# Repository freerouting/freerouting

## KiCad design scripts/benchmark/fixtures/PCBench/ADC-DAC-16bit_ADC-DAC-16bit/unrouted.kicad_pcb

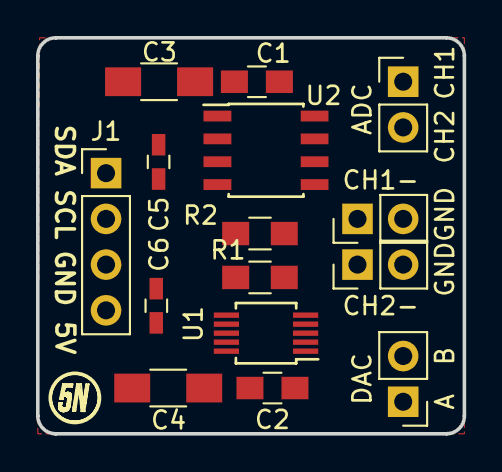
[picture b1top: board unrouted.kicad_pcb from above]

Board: 2 copper layers, 23.7 x 22.0 mm, 16 parts (1 on the bottom side), 11 nets, no tracks yet.

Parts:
C1, C2: 100n; C_0805_HandSoldering
C3, C4: 10u; C_1206_HandSoldering
C5, C6: 100n; C_0603_HandSoldering
J1: CON; Pin_Header_Straight_1x04_Pitch2.54mm
J2: DAC; Pin_Header_Straight_1x02_Pitch2.54mm
J3: ADC; Pin_Header_Straight_1x02_Pitch2.54mm
J4: CH1-; Pin_Header_Straight_1x02_Pitch2.54mm
J5: CH2-; Pin_Header_Straight_1x02_Pitch2.54mm
R1, R2: 4K7; R_0805_HandSoldering
TP1: DAC Vref; Measurement_Point_Round-SMD-Pad_Small
U1: AD5667R; MSOP-10_3x3mm_Pitch0.5mm
U2: MCP3426; SOIC-8_3.9x4.9mm_Pitch1.27mm

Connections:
+5V: C1.1, C2.1, C3.1, C4.1, C5.1, C6.1, J1.4, R1.1, R2.1, U1.5, U1.9, U2.3
GND: C1.2, C2.2, C3.2, C4.2, C5.2, C6.2, J1.3, J4.2, J5.2, U1.3, U1.4, U1.6, U2.6
unnamed: J1.1, R1.2, U1.8, U2.4
unnamed: J1.2, R2.2, U1.7, U2.5
unnamed: J2.1, U1.1
unnamed: J2.2, U1.2
unnamed: J3.1, U2.1
unnamed: J3.2, U2.7
unnamed: J4.1, U2.2
unnamed: J5.1, U2.8
unnamed: TP1.1, U1.10

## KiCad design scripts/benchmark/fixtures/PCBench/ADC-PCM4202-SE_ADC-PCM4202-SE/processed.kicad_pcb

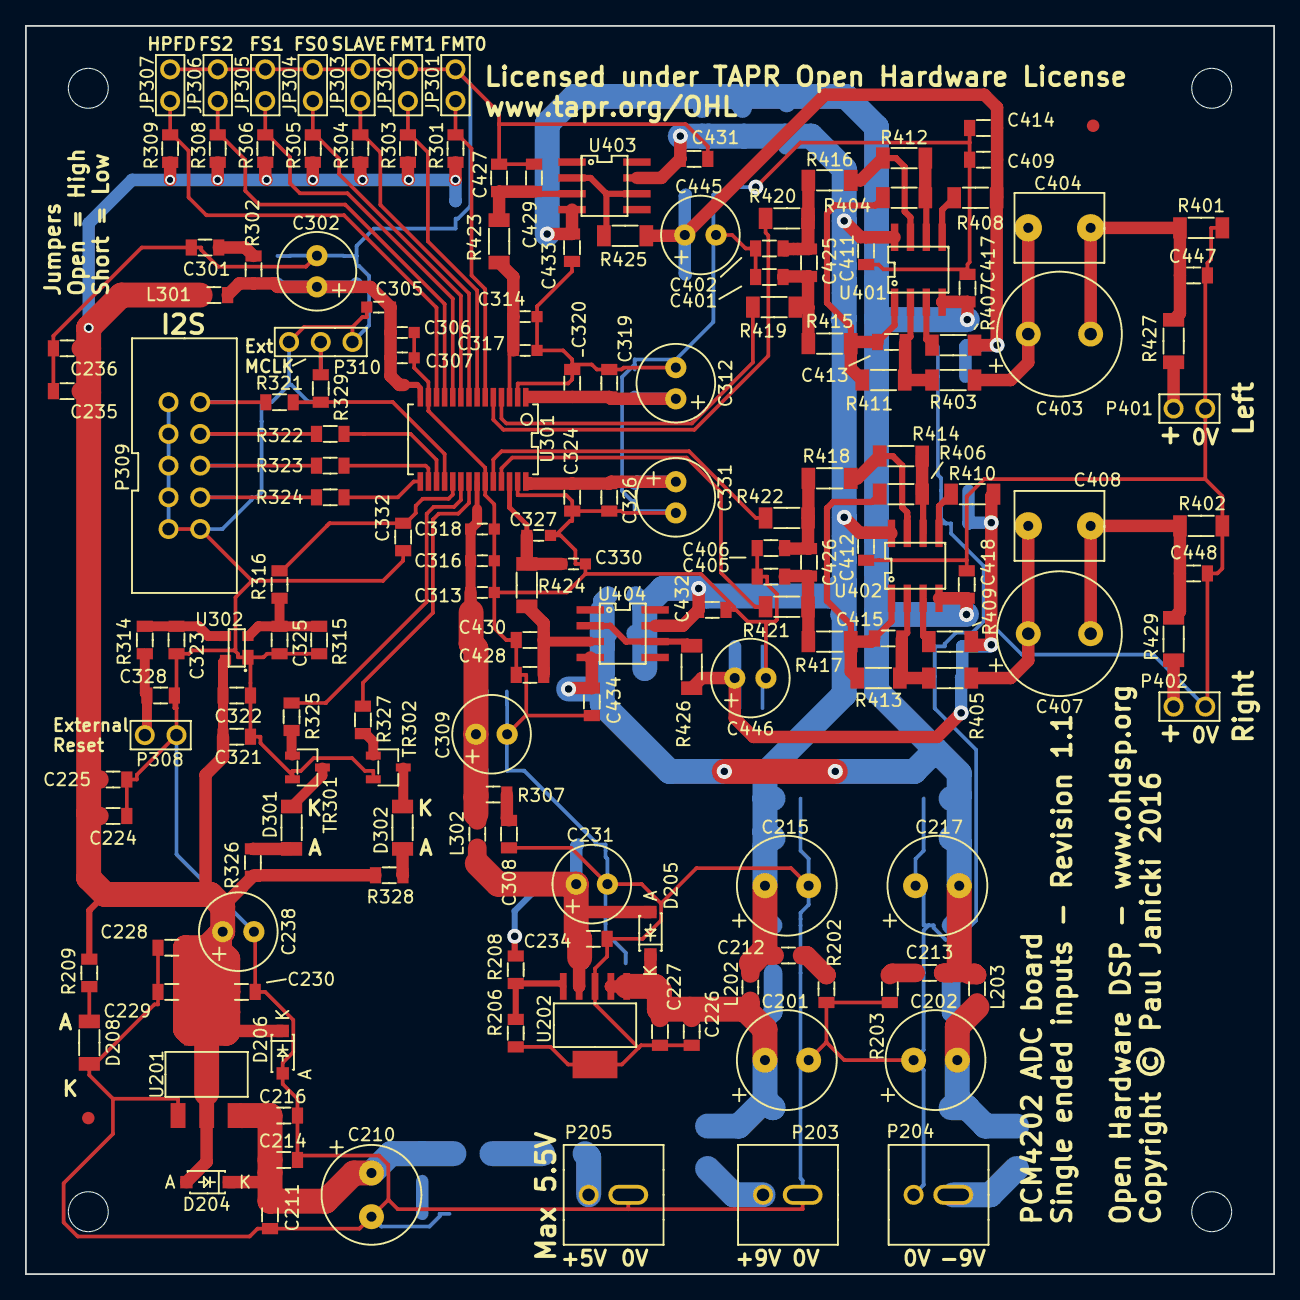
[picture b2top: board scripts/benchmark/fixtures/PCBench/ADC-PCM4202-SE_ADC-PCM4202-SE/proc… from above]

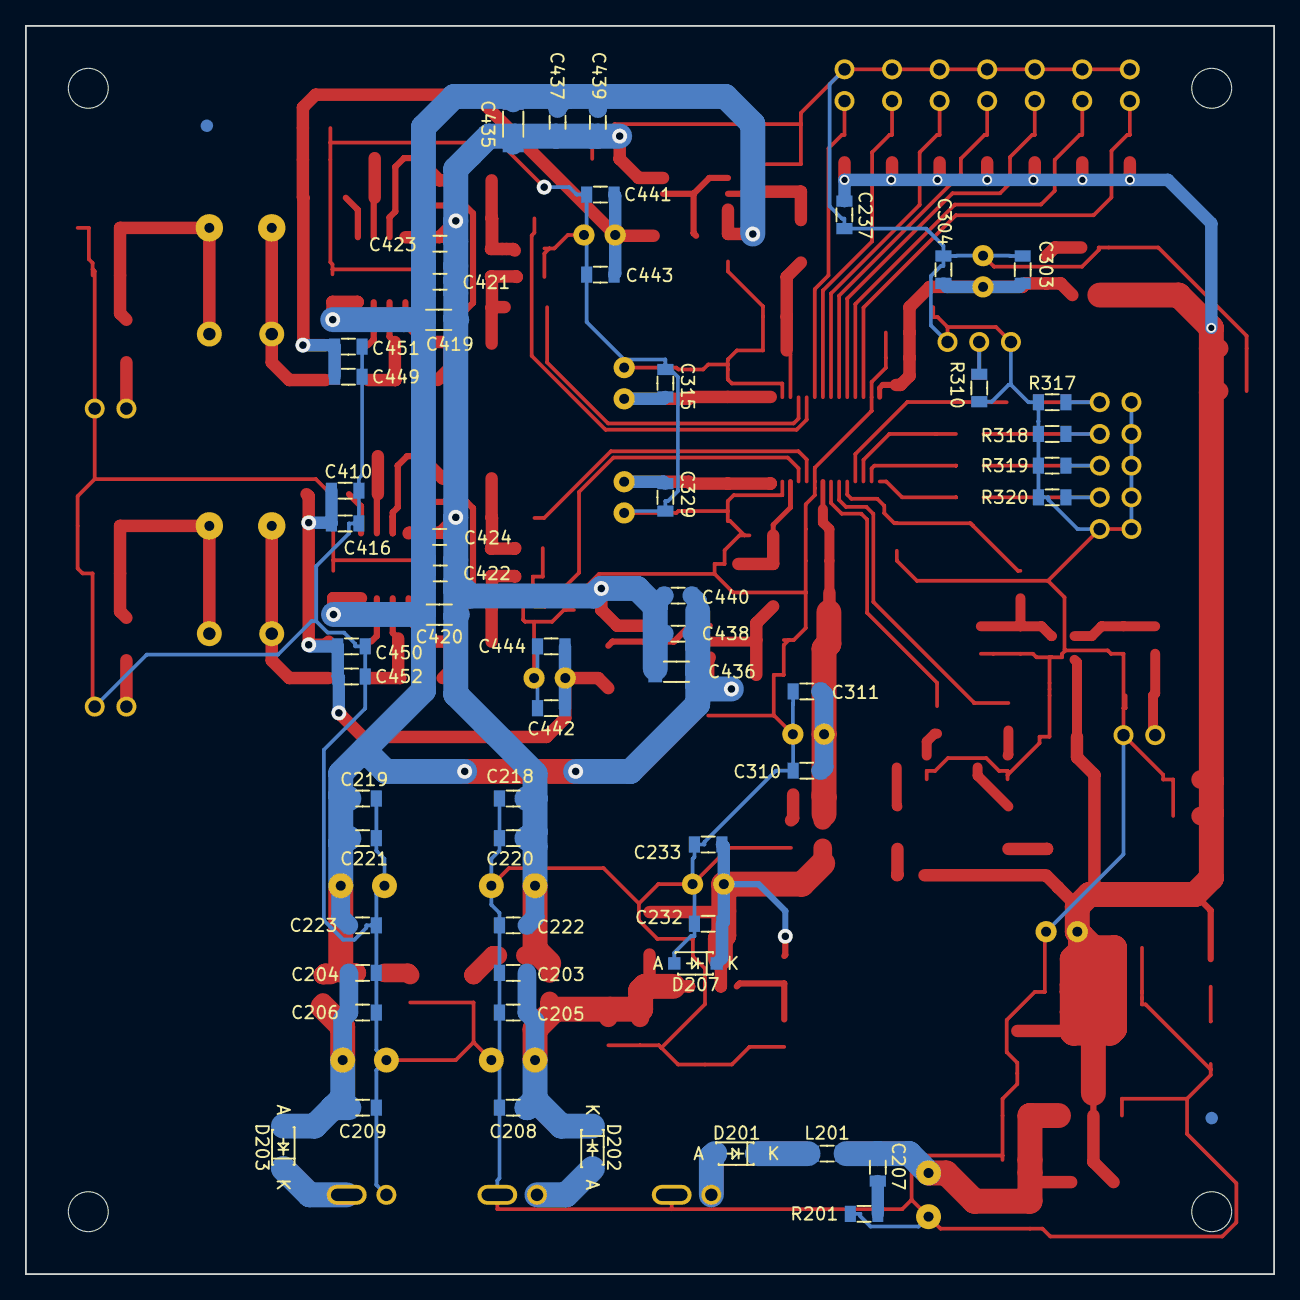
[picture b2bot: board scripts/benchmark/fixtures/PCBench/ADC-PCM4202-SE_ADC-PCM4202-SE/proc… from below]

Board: 2 copper layers, 100.0 x 100.0 mm, 230 parts (57 on the bottom side), 85 nets.

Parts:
C201, C202, C210, C215, C217: 220u; CAP-TH-D8mmP3.5mm
C203, C204, C211, C218, C219, C226, C228, C232, C303, C310, C315, C329: 22u; SMD-0805
C205, C206, C214, C220, C221, C225, C227, C229, C233, C236, C237, C304, C311, C319, C322, C323, C326, C328, C332, C409, C410, C411, C412, C417, C418, C421, C422, C427, C428, C431, C432, C433, C434, C437, C438, C441, C442, C449, C450: 100n; SMD-0805
C207, C212, C213, C301, C308, C401, C402, C405, C406: 100p; SMD-0805
C208, C209, C216, C222, C223, C230, C234, C320, C324, C423, C424, C429, C430, C439, C440, C443, C444: 10n; SMD-0805
C224, C235, C321, C414, C416, C451, C452: 10u; SMD-0805
C231, C238, C302, C309, C312, C331: 220u; CAP-TH-D6.3mmP2.5mm
C305, C313: 1u; SMD-0603
C306, C314, C316, C330: 100n; SMD-0603
C307, C317, C318, C327: 10n; SMD-0603
C325: N/F; SMD-0805
C403, C407: 100u; CAP-TH-D10mmP5mm
C404, C408: 100n; CAP_TH_5mm
C413, C415: 330p; SMD-0805
C419, C420, C435, C436: 10u; SMD-1206
C425, C426: 2n7; SMD-0805
C445, C446: 47u; CAP-TH-D6.3mmP2.5mm
C447, C448: 1n; SMD-0805
D201, D202, D203, D204, D205, D206, D207: SS14L; DIODE-SOD-123
D208: Green LED 1206; SMD-1206
D301, D302: Red LED 1206; SMD-1206
FID1, FID2, FID3, FID4: MNT_HOLE; FID-1MM-3MM
JP301, JP302, JP303, JP304, JP305, JP306, JP307: CONN_2x1; CONN_SIL_2_1MM
L201, L202, L203, L301, L302: 600R@100MHz; SMD-0805
MNT201, MNT202, MNT203, MNT204: MNT_HOLE; MNT_HOLE_3.2mm
P203, P204, P205: CONN_2x1; CONN-2WAY-2.54mm-3.81mm-SPACING
P308, P401, P402: CONN_2x1; CONN_SIL_2_1MM
P309: CONN_02X05; CONN_DIL_2X5_BOX_1MM
P310: N/F; CONN_SIL_3_1MM
R201, R202, R203, R302, R307: 47; SMD-0805
R206: 2k2; SMD-0805
R208: 6k8; SMD-0805
R209, R326, R328: 470; SMD-0805
R301, R303, R304, R305, R306, R308, R309: 10k; SMD-0805
R310, R317, R318, R319, R320, R329: N/F; SMD-0805
R314, R325, R327: 1k; SMD-0805
R315: 100k; SMD-0805
R316: 100R; SMD-0805
R321, R322, R323: 0; SMD-0805
R324: 75; SMD-0805
R401, R402: 47k; SMD-1206
R403, R405, R423, R424, R425, R426, R427, R429: 1k; SMD-1206
R404, R406, R412, R414: 1k5; SMD-1206
R407, R408, R409, R410, R411, R413: 2k2; SMD-1206
R415, R416, R417, R418: 40R2; SMD-1206
R419, R420: 100; SMD-1206
R421, R422: 100R; SMD-1206
TR301, TR302: BC847; IC-SOT23
U201: TLV1117LV33DCY; IC-SOT-223
U202: TPS7A4501; IC-SOT223-6
U301: PCM4202DBT; IC-SSOP28
U302: ADM811TART; IC-SOT143
U401, U402: TLE2072; IC_SOIC_8
U403, U404: TLE2071; IC_SOIC_8

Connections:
+9VA: C212.1, C215.1, C218.1, C220.1, C222.1, C411.1, C412.1, C419.1, C420.1, C421.1, C422.1, C423.1, C424.1, C431.1, C432.1, C435.1, C436.1, C437.1, C438.1, C439.1, C440.1, L202.2, U401.8, U402.8, U403.7, U404.7
-9VA: C213.2, C217.2, C219.2, C221.2, C223.2, C417.2, C418.2, C419.2, C420.2, C421.2, C422.2, C423.2, C424.2, C433.2, C434.2, C435.2, C436.2, C437.2, C438.2, C439.2, C440.2, L203.2, U401.4, U402.4, U403.4, U404.4
/InputFilters/ANAL+: R419.1, U301.4
/InputFilters/ANAL-: R420.1, U301.5
/InputFilters/ANAR+: R421.1, U301.25
/InputFilters/ANAR-: R422.1, U301.24
/InputFilters/VCML: C409.1, C414.1, C441.1, C443.1, C445.1, C449.1, C451.1, R407.2, R408.2, R425.1
/InputFilters/VCMR: C410.1, C416.1, C442.1, C444.1, C446.1, C450.1, C452.1, R409.2, R410.2, R426.1
/InputFilters/VCOML: C314.1, C317.1, R423.2, U301.3
/InputFilters/VCOMR: C327.1, C330.1, R424.2, U301.26
/PCM4202/ADC_RESET: C332.1, R316.1, U301.19
/PCM4202/AVCC: C309.1, C310.1, C311.1, C313.1, C316.1, C318.1, L302.2, R307.1, U301.22
/PCM4202/CLIPL: R327.1, U301.21
/PCM4202/CLIPR: R325.1, U301.20
/PCM4202/DVDD: C302.1, C303.1, C304.1, C305.1, C306.1, C307.1, L301.2, R302.1, U301.14
/PCM4202/FMT0: JP301.1, R301.2, U301.6
/PCM4202/FMT1: JP302.1, R303.2, U301.7
/PCM4202/FS0: JP304.1, R305.2, U301.9
/PCM4202/FS1: JP305.1, R306.2, U301.10
/PCM4202/FS2: JP306.1, R308.2, U301.11
/PCM4202/HPFD: JP307.1, R309.2, U301.12
/PCM4202/SLAVE: JP303.1, R304.2, U301.8
GNDA: C201.2, C202.1, C203.2, C204.1, C205.2, C206.1, C208.2, C209.1, C210.2, C211.2, C214.2, C215.2, C216.2, C217.1, C218.2, C219.1, C220.2, C221.1, C222.2, C223.1, C224.2, C225.2, C226.2, C227.2, C228.2, C229.2, C230.2, C231.2, C232.2, C233.2, C234.2, C235.2, C236.2, C237.2, C238.2, C301.2, C302.2, C303.2, C304.2, C305.2, C306.2, C307.2, C308.2, C309.2, C310.2, C311.2, C312.2, C313.2, C314.2, C315.2, C316.2, C317.2, C318.2, C319.2, C320.2, C321.2, C322.2, C323.2, C324.2, C325.2, C326.2, C327.2, C328.2, C329.2, C330.2, C331.2, C332.2, C401.1, C402.2, C405.1, C406.2, C409.2, C410.2, C411.2, C412.2, C414.2, C416.2, C417.1, C418.1, C427.2, C428.2, C429.2, C430.2, C431.2, C432.2, C433.1, C434.1, C441.2, C442.2, C443.2, C444.2, C445.2, C446.2, C447.2, C448.2, C449.2, C450.2, C451.2, C452.2, D206.1, D207.1, D208.2, JP301.2, JP302.2, JP303.2, JP304.2, JP305.2, JP306.2, JP307.2, P203.2, P204.1, P205.2, P308.2, P309.1, P309.3, P309.5, P309.7, P309.9, P309.10, P310.1, P310.3, P401.2, P402.2, R201.2, R202.2, R203.1, R206.2, R310.1, R315.1, R317.1, R318.1, R319.1, R320.1, R401.1, R402.1, TR301.2, TR302.2, U201.1, U202.3, U301.2, U301.13, U301.23, U301.27, U302.1
unnamed: C202.2, C204.2, C206.2, C209.2, D203.1, L203.1
unnamed: C207.1, C210.1, C211.1, C214.1, C216.1, D204.2, L201.2, U201.3
unnamed: C207.2, R201.1
unnamed: C212.2, R202.1
unnamed: C213.1, R203.2
unnamed: C301.1, R302.2
unnamed: C308.1, R307.2
unnamed: C312.1, C315.1, C319.1, C320.1, U301.1
unnamed: C323.1, R314.1, U302.3
unnamed: C324.1, C326.1, C329.1, C331.1, U301.28
unnamed: C325.1, R315.2, R316.2, U302.2
unnamed: C328.1, P308.1, R314.2
unnamed: C401.2, C425.1, R415.1, R419.2
unnamed: C402.1, C425.2, R416.1, R420.2
unnamed: C403.1, C404.2, R403.2
unnamed: C403.2, C404.1, C447.1, R401.2, R427.1
unnamed: C405.2, C426.1, R417.1, R421.2
unnamed: C406.1, C426.2, R418.1, R422.2
unnamed: C407.1, C408.2, R405.2
unnamed: C407.2, C408.1, C448.1, R402.2, R429.1
unnamed: C413.1, R403.1, R411.2, U401.2
unnamed: C413.2, R404.1, R411.1, R415.2, U401.1
unnamed: C415.1, R405.1, R413.2, U402.2
unnamed: C415.2, R406.1, R413.1, R417.2, U402.1
unnamed: C427.1, C429.1, R423.1, U403.3
unnamed: C428.1, C430.1, R424.1, U404.3
unnamed: D201.1, P205.1
unnamed: D201.2, L201.1
unnamed: D202.1, P203.1
unnamed: D203.2, P204.2
unnamed: D208.1, R209.1
unnamed: D301.1, R326.1
unnamed: D301.2, TR301.3
unnamed: D302.1, R328.1
unnamed: D302.2, TR302.3
unnamed: P309.2, R317.2, R321.1
unnamed: P309.4, R318.2, R322.1
unnamed: P309.6, R319.2, R323.1
unnamed: P309.8, R320.2, R324.1
unnamed: P310.2, R310.2, R329.1
unnamed: P401.1, R427.2
unnamed: P402.1, R429.2
unnamed: R206.1, R208.2, U202.5
unnamed: R321.2, R329.2, U301.18
unnamed: R322.2, U301.17
unnamed: R323.2, U301.16
unnamed: R324.2, U301.15
unnamed: R325.2, TR301.1
unnamed: R327.2, TR302.1
unnamed: R404.2, R412.2, U401.6
unnamed: R406.2, R414.2, U402.6
unnamed: R407.1, U401.3
unnamed: R408.1, U401.5
unnamed: R409.1, U402.3
unnamed: R410.1, U402.5
unnamed: R412.1, R416.2, U401.7
unnamed: R414.1, R418.2, U402.7
unnamed: R425.2, U403.2, U403.6
unnamed: R426.2, U404.2, U404.6
VAA: C231.1, C232.1, C233.1, C234.1, D205.1, D207.2, L302.1, R208.1, U202.4
VCC: C201.1, C203.1, C205.1, C208.1, C226.1, C227.1, D202.2, D205.2, L202.1, U202.1, U202.2
VDD: C224.1, C225.1, C228.1, C229.1, C230.1, C235.1, C236.1, C237.1, C238.1, C321.1, C322.1, D204.1, D206.2, L301.1, R209.2, R301.1, R303.1, R304.1, R305.1, R306.1, R308.1, R309.1, R326.2, R328.2, U201.2, U302.4

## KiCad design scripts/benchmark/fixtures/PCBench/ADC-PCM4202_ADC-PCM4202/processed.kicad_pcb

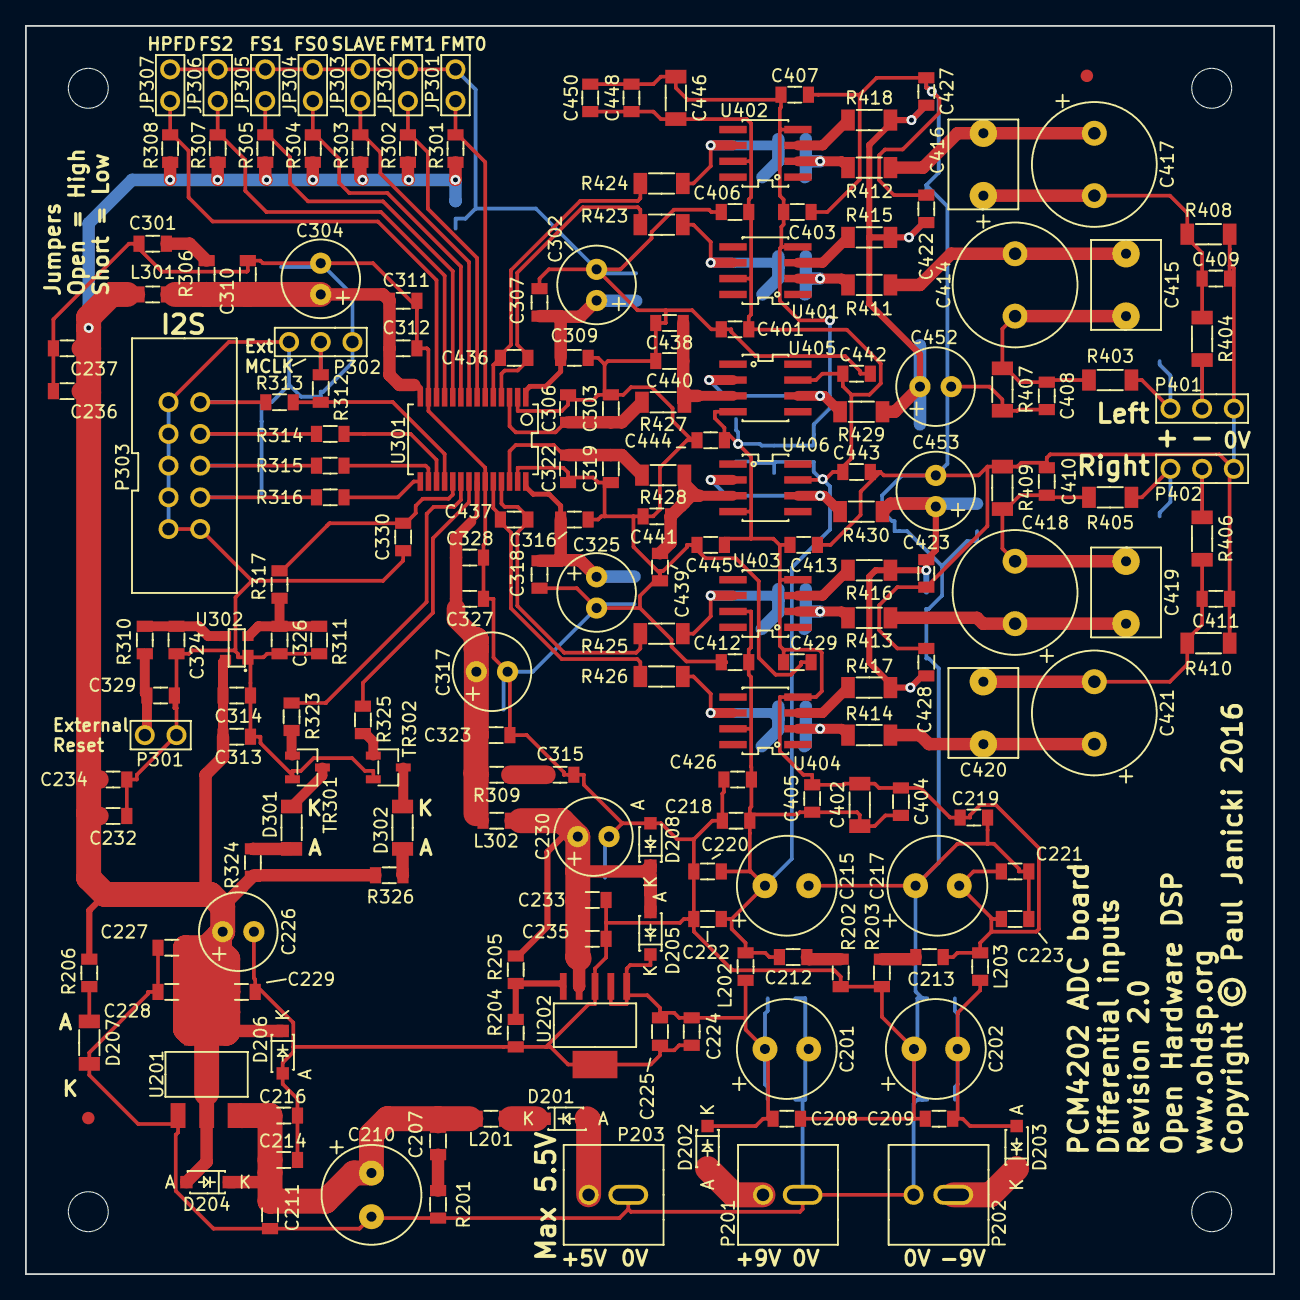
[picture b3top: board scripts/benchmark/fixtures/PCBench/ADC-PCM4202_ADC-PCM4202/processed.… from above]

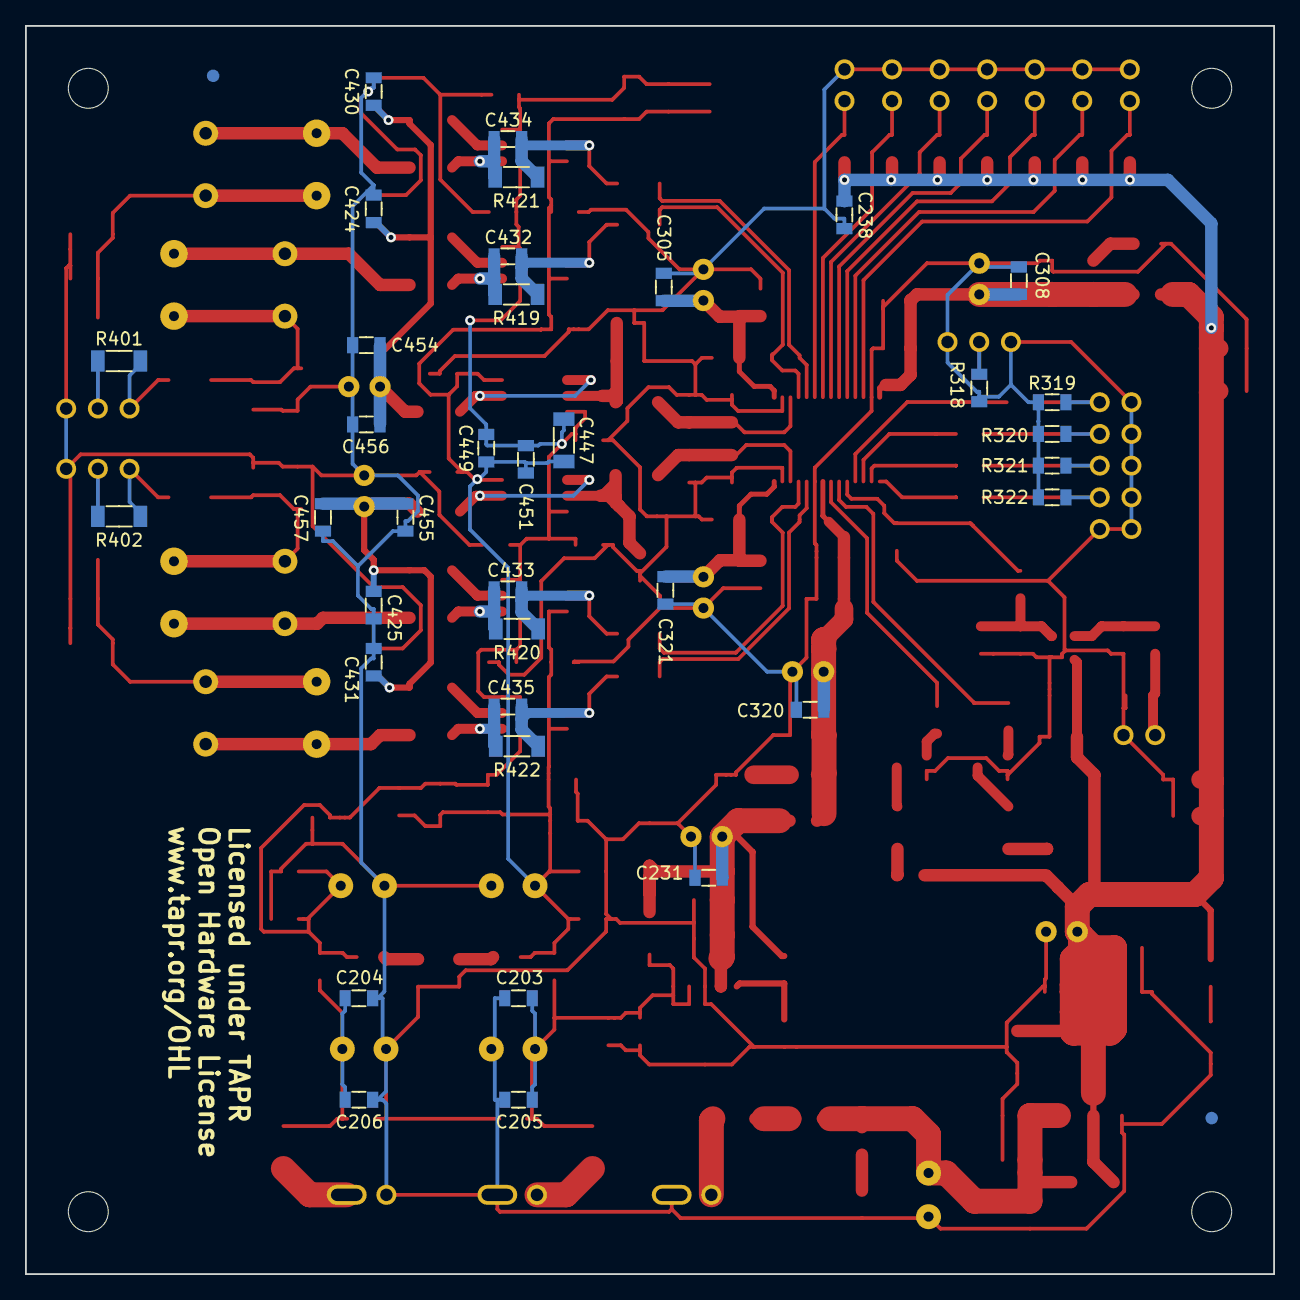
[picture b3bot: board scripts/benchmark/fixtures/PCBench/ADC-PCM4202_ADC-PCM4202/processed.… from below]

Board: 2 copper layers, 100.0 x 100.0 mm, 237 parts (38 on the bottom side), 87 nets.

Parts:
C201, C202, C210, C215, C217: 220u; CAP-TH-D8mmP3.5mm
C203, C204, C211, C218, C219, C224, C227, C231, C305, C308, C320, C321: 22u; SMD-0805
C205, C206, C214, C220, C221, C225, C228, C233, C234, C237, C238, C303, C307, C310, C311, C314, C318, C322, C323, C324, C327, C329, C330, C401, C403, C404, C406, C407, C412, C413, C422, C423, C426, C427, C428, C429, C438, C439, C442, C443, C444, C445, C448, C449, C454, C455: 100n; SMD-0805
C207, C212, C213, C301, C315, C408, C409, C410, C411: 100p; SMD-0805
C208, C209, C216, C222, C223, C229, C235, C306, C309, C312, C316, C319, C328, C405, C440, C441, C450, C451, C456, C457: 10n; SMD-0805
C226, C230, C302, C304, C317, C325: 220u; CAP-TH-D6.3mmP2.5mm
C232, C236, C313, C424, C425, C430, C431: 10u; SMD-0805
C326: N/F; SMD-0805
C402, C446, C447: 10u; SMD-1206
C414, C417, C418, C421: 100u; CAP-TH-D10mmP5mm
C415, C416, C419, C420: 100n; CAP_TH_5mm
C432, C433, C434, C435: 47p; SMD-0805
C436, C437: 2n7; SMD-0805
C452, C453: 47u; CAP-TH-D6.3mmP2.5mm
D201, D202, D203, D204, D205, D206, D208: SS14L; DIODE-SOD-123
D207: Green LED 1206; SMD-1206
D301, D302: Red LED 1206; SMD-1206
FID201, FID202, FID203, FID204: MNT_HOLE; FID-1MM-3MM
JP301, JP302, JP303, JP304, JP305, JP306, JP307: CONN_2x1; CONN_SIL_2_1MM
L201, L202, L203, L301, L302: 600R@100MHz; SMD-0805
MNT201, MNT202, MNT203, MNT204: MNT_HOLE; MNT_HOLE_3.2mm
P201, P202, P203: CONN_2x1; CONN-2WAY-2.54mm-3.81mm-SPACING
P301: CONN_2x1; CONN_SIL_2_1MM
P302: N/F; CONN_SIL_3_1MM
P303: CONN_02X05; CONN_DIL_2X5_BOX_1MM
P401, P402: CONN_3x1; CONN_SIL_3_1MM
R201, R202, R203, R306, R309: 47; SMD-0805
R204: 2k2; SMD-0805
R205: 6k8; SMD-0805
R206, R324, R326: 470; SMD-0805
R301, R302, R303, R304, R305, R307, R308: 10k; SMD-0805
R310, R323, R325: 1k; SMD-0805
R311: 100k; SMD-0805
R312, R318, R319, R320, R321, R322: N/F; SMD-0805
R313, R314, R315: 0; SMD-0805
R316: 75; SMD-0805
R317: 100R; SMD-0805
R401, R402, R419, R420, R421, R422: 10k; SMD-1206
R403, R404, R405, R406: 100; SMD-1206
R407, R408, R409, R410: 100k; SMD-1206
R411, R412, R413, R414, R415, R416, R417, R418: 4k7; SMD-1206
R423, R424, R425, R426: 40R2; SMD-1206
R427, R428, R429, R430: 1k; SMD-1206
TR301, TR302: BC847; IC-SOT23
U201: TLV1117LV33DCY; IC-SOT-223
U202: TPS7A4501; IC-SOT223-6
U301: PCM4202DBT; IC-SSOP28
U302: ADM811TART; IC-SOT143
U401, U402, U403, U404, U405, U406: TLE2071; IC_SOIC_8

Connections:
+9VA: C212.1, C215.1, C218.1, C220.1, C222.1, C401.1, C402.1, C404.1, C405.1, C406.1, C412.1, C426.1, C442.1, C443.1, C446.1, C447.1, C448.1, C449.1, C450.1, C451.1, L202.2, U401.7, U402.7, U403.7, U404.7, U405.7, U406.7
-9VA: C213.2, C217.2, C219.2, C221.2, C223.2, C402.2, C403.2, C404.2, C405.2, C407.2, C413.2, C429.2, C444.2, C445.2, C446.2, C447.2, C448.2, C449.2, C450.2, C451.2, L203.2, U401.4, U402.4, U403.4, U404.4, U405.4, U406.4
/InputFilters/ANAL+: C436.1, R423.1, U301.4
/InputFilters/ANAL-: C436.2, R424.1, U301.5
/InputFilters/ANAR+: C437.1, R425.1, U301.25
/InputFilters/ANAR-: C437.2, R426.1, U301.24
/InputFilters/VCML: C422.1, C424.1, C427.1, C430.1, C452.1, C454.1, C456.1, R415.1, R418.2, R429.1
/InputFilters/VCMR: C423.1, C425.1, C428.1, C431.1, C453.1, C455.1, C457.1, R416.1, R417.2, R430.1
/InputFilters/VCOML: C303.1, C306.1, R427.2, U301.3
/InputFilters/VCOMR: C319.1, C322.1, R428.2, U301.26
/PCM4202/ADC_RESET: C330.1, R317.1, U301.19
/PCM4202/AVCC: C317.1, C320.1, C323.1, C327.1, C328.1, L302.2, R309.1, U301.22
/PCM4202/CLIPL: R325.1, U301.21
/PCM4202/CLIPR: R323.1, U301.20
/PCM4202/DVDD: C304.1, C308.1, C310.1, C311.1, C312.1, L301.2, R306.1, U301.14
/PCM4202/FMT0: JP301.1, R301.2, U301.6
/PCM4202/FMT1: JP302.1, R302.2, U301.7
/PCM4202/FS0: JP304.1, R304.2, U301.9
/PCM4202/FS1: JP305.1, R305.2, U301.10
/PCM4202/FS2: JP306.1, R307.2, U301.11
/PCM4202/HPFD: JP307.1, R308.2, U301.12
/PCM4202/SLAVE: JP303.1, R303.2, U301.8
GNDA: C201.2, C202.1, C203.2, C204.1, C205.2, C206.1, C208.2, C209.1, C210.2, C211.2, C214.2, C215.2, C216.2, C217.1, C218.2, C219.1, C220.2, C221.1, C222.2, C223.1, C224.2, C225.2, C226.2, C227.2, C228.2, C229.2, C230.2, C231.2, C232.2, C233.2, C234.2, C235.2, C236.2, C237.2, C238.2, C301.2, C302.2, C303.2, C304.2, C305.2, C306.2, C307.2, C308.2, C309.2, C310.2, C311.2, C312.2, C313.2, C314.2, C315.2, C316.2, C317.2, C318.2, C319.2, C320.2, C321.2, C322.2, C323.2, C324.2, C325.2, C326.2, C327.2, C328.2, C329.2, C330.2, C401.2, C403.1, C406.2, C407.1, C408.2, C409.2, C410.2, C411.2, C412.2, C413.1, C422.2, C423.2, C424.2, C425.2, C426.2, C427.2, C428.2, C429.1, C430.2, C431.2, C438.2, C439.2, C440.2, C441.2, C442.2, C443.2, C444.1, C445.1, C452.2, C453.2, C454.2, C455.2, C456.2, C457.2, D206.1, D207.2, D208.1, JP301.2, JP302.2, JP303.2, JP304.2, JP305.2, JP306.2, JP307.2, P201.2, P202.1, P203.2, P301.2, P302.1, P302.3, P303.1, P303.3, P303.5, P303.7, P303.9, P303.10, P401.3, P402.3, R201.2, R202.2, R203.1, R204.2, R311.1, R318.1, R319.1, R320.1, R321.1, R322.1, R407.1, R408.1, R409.1, R410.1, TR301.2, TR302.2, U201.1, U202.3, U301.2, U301.13, U301.23, U301.27, U302.1
unnamed: C202.2, C204.2, C206.2, C209.2, D203.1, L203.1
unnamed: C207.1, C210.1, C211.1, C214.1, C216.1, D204.2, L201.2, U201.3
unnamed: C207.2, R201.1
unnamed: C212.2, R202.1
unnamed: C213.1, R203.2
unnamed: C301.1, R306.2
unnamed: C302.1, C305.1, C307.1, C309.1, U301.1
unnamed: C315.1, R309.2
unnamed: C316.1, C318.1, C321.1, C325.1, U301.28
unnamed: C324.1, R310.1, U302.3
unnamed: C326.1, R311.2, R317.2, U302.2
unnamed: C329.1, P301.1, R310.2
unnamed: C408.1, C414.2, C415.1, R403.1, R407.2
unnamed: C409.1, C416.1, C417.2, R404.1, R408.2
unnamed: C410.1, C418.2, C419.1, R405.1, R409.2
unnamed: C411.1, C420.1, C421.2, R406.1, R410.2
unnamed: C414.1, C415.2, R411.1
unnamed: C416.2, C417.1, R412.2
unnamed: C418.1, C419.2, R413.1
unnamed: C420.2, C421.1, R414.2
unnamed: C432.1, R411.2, R419.2, U401.2
unnamed: C432.2, R419.1, R423.2, U401.6
unnamed: C433.1, R413.2, R420.2, U403.2
unnamed: C433.2, R420.1, R425.2, U403.6
unnamed: C434.1, R412.1, R421.2, U402.2
unnamed: C434.2, R421.1, R424.2, U402.6
unnamed: C435.1, R414.1, R422.2, U404.2
unnamed: C435.2, R422.1, R426.2, U404.6
unnamed: C438.1, C440.1, R427.1, U405.3
unnamed: C439.1, C441.1, R428.1, U406.3
unnamed: D201.1, P203.1
unnamed: D201.2, L201.1
unnamed: D202.1, P201.1
unnamed: D203.2, P202.2
unnamed: D207.1, R206.1
unnamed: D301.1, R324.1
unnamed: D301.2, TR301.3
unnamed: D302.1, R326.1
unnamed: D302.2, TR302.3
unnamed: P302.2, R312.1, R318.2
unnamed: P303.2, R313.1, R319.2
unnamed: P303.4, R314.1, R320.2
unnamed: P303.6, R315.1, R321.2
unnamed: P303.8, R316.1, R322.2
unnamed: P401.1, R401.2, R403.2
unnamed: P401.2, R401.1, R404.2
unnamed: P402.1, R402.2, R405.2
unnamed: P402.2, R402.1, R406.2
unnamed: R204.1, R205.2, U202.5
unnamed: R312.2, R313.2, U301.18
unnamed: R314.2, U301.17
unnamed: R315.2, U301.16
unnamed: R316.2, U301.15
unnamed: R323.2, TR301.1
unnamed: R325.2, TR302.1
unnamed: R415.2, U401.3
unnamed: R416.2, U403.3
unnamed: R417.1, U404.3
unnamed: R418.1, U402.3
unnamed: R429.2, U405.2, U405.6
unnamed: R430.2, U406.2, U406.6
VAA: C230.1, C231.1, C233.1, C235.1, D205.1, D208.2, L302.1, R205.1, U202.4
VCC: C201.1, C203.1, C205.1, C208.1, C224.1, C225.1, D202.2, D205.2, L202.1, U202.1, U202.2
VDD: C226.1, C227.1, C228.1, C229.1, C232.1, C234.1, C236.1, C237.1, C238.1, C313.1, C314.1, D204.1, D206.2, L301.1, R206.2, R301.1, R302.1, R303.1, R304.1, R305.1, R307.1, R308.1, R324.2, R326.2, U201.2, U302.4

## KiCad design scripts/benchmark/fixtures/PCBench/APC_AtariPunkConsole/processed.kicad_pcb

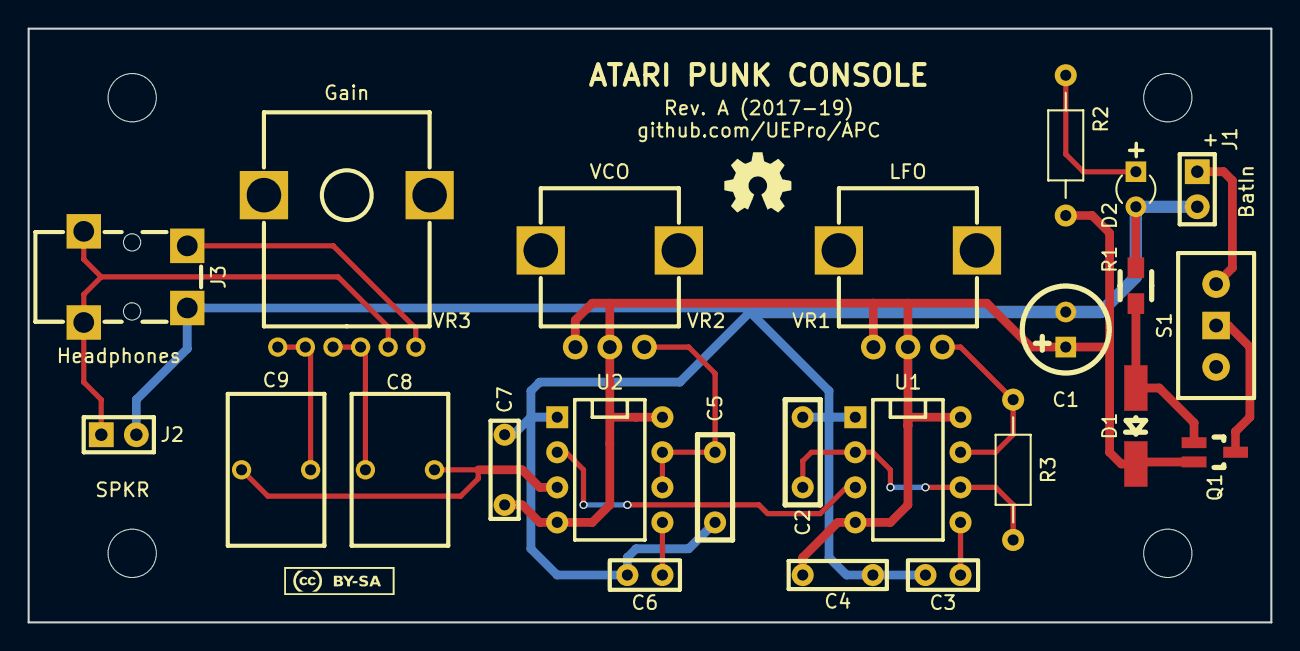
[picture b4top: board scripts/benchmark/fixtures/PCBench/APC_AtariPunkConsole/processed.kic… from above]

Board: 2 copper layers, 90.0 x 43.0 mm, 30 parts (0 on the bottom side), 17 nets.

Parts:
C1: 220µ/16V; C_round-radial-polar-2,5mm-6,3mm
C2: 10n; C_rect-radial-bipolar-200mil-2,5x7mm
C3, C6: 10n; C_rect-radial-bipolar-100mil-2x5mm
C4, C7: 100n; C_rect-radial-bipolar-200mil-2x7,5mm
C5: 100n; C_rect-radial-bipolar-200mil-2,5x7mm
C8, C9: 2µ2; C-Rect_L7_W11_P5
D1: 4V7; Diode_MiniMELF-Handsoldering
D2: 3mm/cyan; LED_2pin-3mm
Des*: Val*; MountingHole-3,5mm
Des*_2, Des*_3, Des*_4: Val*; MountingHole-3,5mm
J1: BatIn; PinArray-100mil-1x2
J2: Speaker; PinArray-100mil-1x2
J3: Klinke-stereo; Lumberg-1503-07-Klinke-3,5mm
Q1: FDN304; SOT23-Handsoldering
R1: 10k; SMD0805-HandSoldering
R2: 10k; R_axial_400mil
R3: 1k; R_axial_400mil
S1: S_1P2T; S-Schiebeschalter_China_SPDT
U1, U2: NE555; DIP-8_300
VAL: REF; oshw5mm
VAL_2: REF; CC-BY-SA_08mm_Fsi
VR1, VR2: 500k; VR-vert_PCB_china
VR3: 10k log; VR-Alps_R12L_vert

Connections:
+9V: C1.1, C4.1, C7.1, D1.2, Q1.2, R2.1, U1.4, U1.8, U2.4, U2.8, VR1.1, VR1.2, VR2.1, VR2.2
GND: C1.2, C2.2, C3.2, C4.2, C5.2, C6.2, C7.2, D2.2, J1.2, J2.2, J3.1, R1.2, U1.1, U2.1
unnamed: C2.1, R3.1, U1.2, U1.6
unnamed: C3.1, U1.5
unnamed: C5.1, U2.6, U2.7, VR2.3
unnamed: C6.1, U2.5
unnamed: C8.1, C9.1, U2.3
unnamed: C8.2, VR3.1, VR3.2
unnamed: C9.2, VR3.4, VR3.5
unnamed: D1.1, Q1.1, R1.1
unnamed: D2.1, R2.2
unnamed: J1.1, S1.3
unnamed: J2.1, J3.3, VR3.3
unnamed: J3.2, VR3.6
unnamed: Q1.3, S1.2
unnamed: R3.2, U1.7, VR1.3
unnamed: U1.3, U2.2

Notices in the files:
scripts/benchmark/fixtures/PCBench/ADC-PCM4202-SE_ADC-PCM4202-SE/processed.kicad_pcb:
Licensed under the TAPR Open Hardware License (www.tapr.org/OHL). This documentation
Copyright Paul Janicki 2016
Copyright © Paul Janicki 2016
Licensed under TAPR Open Hardware License
